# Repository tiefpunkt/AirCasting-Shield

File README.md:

# Aircasting Shield
Airquality sensing sensor shield for Arduino. To be used with Bluetooth Shield, for http://www.aircasting.org/.

## Test on PC
Connect to bluetooth chip via `sudo rfcomm connect /dev/rfcomm0 00:13:EF:12:1C:B2`.
If different chip, get ID via `hcitool scan`

## See also
More information on the build over at http://hackingroom.de/wiki/AirCasting_Shield

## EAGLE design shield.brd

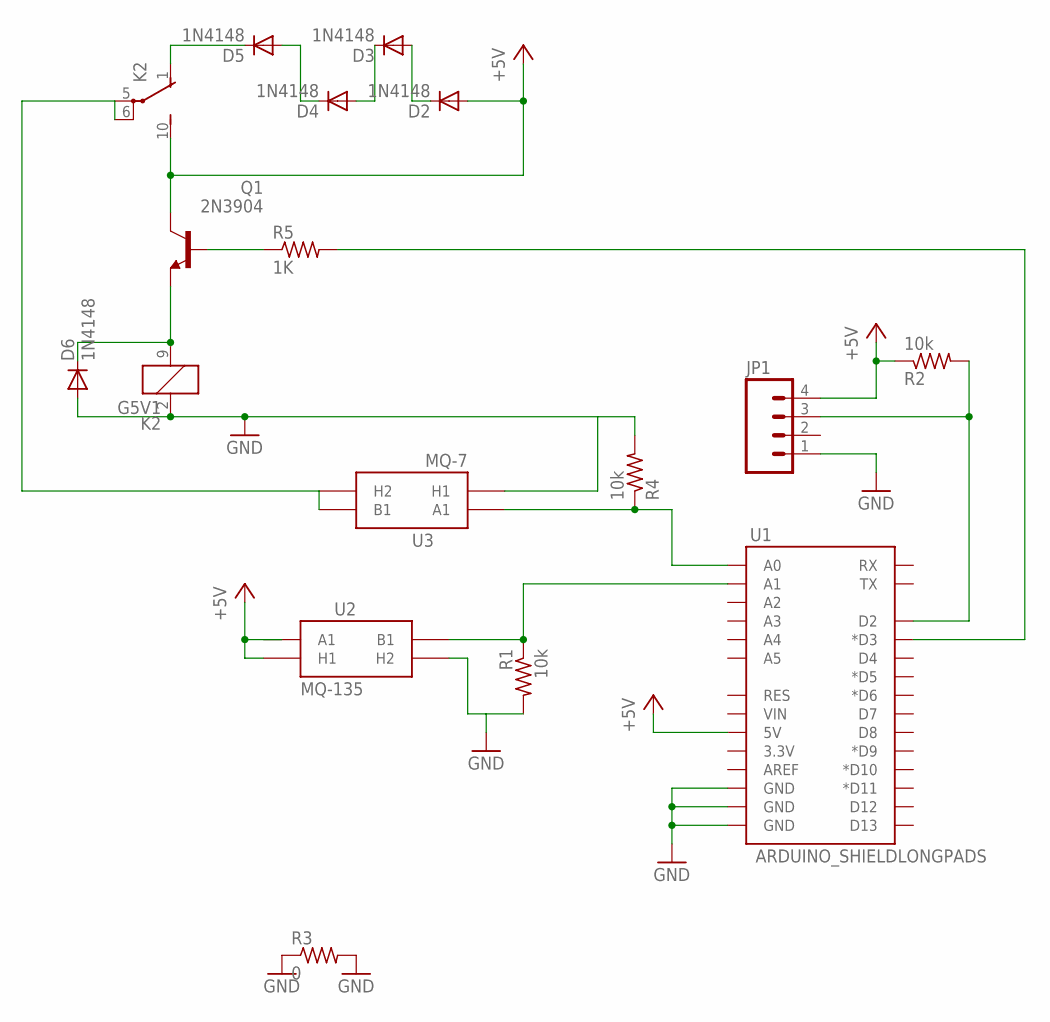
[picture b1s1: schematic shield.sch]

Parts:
D2, D3, D4, D5, D6: 1N4148; DO35-7
JP1: M04LONGPADS; 1X04_LONGPADS
K2: G5V1
Q1: 2N3904; TO92
R1, R2, R4: 10k; 0204/7
R3: 0; 0204/7
R5: 1K; 0204/7
U1: ARDUINO_SHIELDLONGPADS; DUEMILANOVE_SHIELD_LONGPADS
U2: MQ-135; MQ-3
U3: MQ-7; MQ-3

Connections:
+5V: D2.A, JP1.4, K2.10 (S), Q1.1 (C), R2.1, U1.5V, U2.A1, U2.HA (H1)
GND: D6.A, JP1.1, K2.2 (1), R1.2, R3.1, R3.2, R4.2, U1.GND@0 (GND), U1.GND@1 (GND), U1.GND@2 (GND), U2.HB (H2), U3.HA (H1)
unnamed: R5.2, U1.D3 (*D3)
unnamed: R1.1, U1.A1, U2.B1
unnamed: JP1.3, R2.2, U1.D2
unnamed: D2.C, D3.A
unnamed: K2.5, K2.6, U3.B1, U3.HB (H2)
unnamed: D3.C, D4.A
unnamed: D4.C, D5.A
unnamed: D5.C, K2.1 (O)
unnamed: D6.C, K2.9 (2), Q1.3 (E)
unnamed: Q1.2 (B), R5.1
SENSOROUT: R4.1, U1.A0, U3.A1

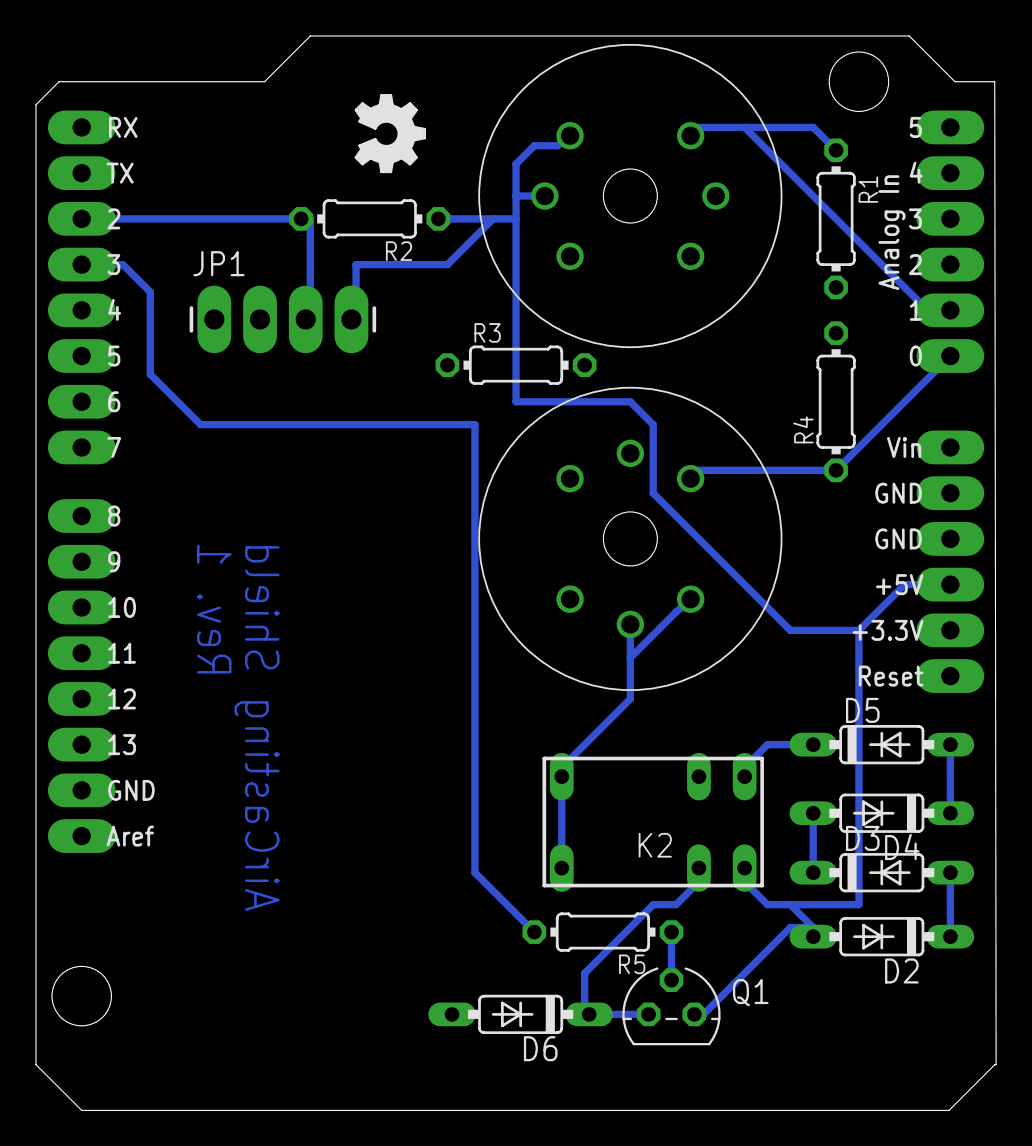
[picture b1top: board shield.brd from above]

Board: 2 copper layers, 53.3 x 59.7 mm, 17 parts (0 on the bottom side), 13 nets.

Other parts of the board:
U$1: OSHW_FILLX150_NOTEXT

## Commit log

2013-08-29 changes to the board
2013-08-29 Arduino sources for rev 1 shield with bluetooth on Arduino Leonardo
2013-08-29 readme, license

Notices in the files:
parts and their libraries:
SparkFun-Boards: Licensing: CC v3.0 Share-Alike You are welcome to use this library for commercial purposes.
